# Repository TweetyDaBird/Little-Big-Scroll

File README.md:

# Little Big Scroll

## A family of low-cost and easy to build macro pads. 
Usable for Media control, macro buttons, or just about anything else you can imagine and code in QMK.

### The 'family' includes:
- **Little Big Scroll 4** - 2 or 4 Cherry MX compatible keys, one Ø40 mm encoder with button, optional OLED. (Complete)
- **Little Big Scroll 6** - 6 Cherry MX compatible keys, one Ø40 mm encoder with button. (Complete)
- **Little Big Scroll 8** - 8 Cherry MX compatible keys, one Ø40 mm encoder with button, optional OLED. (Prototype)
- **Little Big Scroll** - A single Ø40 mm encoder wheel with button. (Prototype completed, pending redesign)

### Common specifications
- Use a Promicro or equivalent controller
- Programmable with QMK and VIAL
- Cherry MX style keyswitches
- Kaihl hot swap sockets
- Clickable Rotary encoder with up to 40mm wheel
- Designed with a complete sandwich case for an easy build (If purchased, comes as a complete kit)
- Optional Per Key RGB / Encoder Underglow
- (LBS 4/8) Optional 0.91" 128x32 OLED screen

## Buildguide

### Step-by-step
- Solder hotswap sockets in markings
- Solder capacitors C1, C2 in markings
- **LSB 4 only** - If you are mounting the OLED, solder Resistors R1, R2 & OLED Screen in place
- Solder Encoder
- Solder controller, face up, flush with underside of PCB (*)
- Assemble plate/spacers around the PCB (**)
- Insert switches/caps (remember to support the sockets!) and add encoder wheel
- Program
- Enjoy!

(*) The controller can be socketed, but that adds height, and you need longer spacers than the ones included if purchasing a kit.

(**) For LSB 4, the unused plate forms the bottom, unless a solid backplate is added as an optional extra. Breakaway tabs need to be removed and filed before use.

## Buy a kit!
I sell complete kits, making it easy to build your keyboard, and it also supports prototypes for new wacky ones. 

## Discord for build help and discussions!

## License

[![CC BY-SA 4.0][cc-by-sa-shield]][cc-by-sa] - This work is licensed under a
[Creative Commons Attribution-ShareAlike 4.0 International License][cc-by-sa].

[cc-by-sa]: http://creativecommons.org/licenses/by-sa/4.0/
[cc-by-sa-shield]: https://img.shields.io/badge/License-CC%20BY--SA%204.0-lightgrey.svg

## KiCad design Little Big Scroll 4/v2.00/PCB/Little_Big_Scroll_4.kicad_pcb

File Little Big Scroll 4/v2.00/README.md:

# Little Big Scroll 4 v2

A low-cost and easy to build macro pad intended for among other things media controls. 

- Uses an RP2040 Zero or equivalent controller
- Programmable with QMK and VIAL
- Cherry MX style keyswitches
- Kaihl hot swap sockets
- Clickable Rotary encoder with up to 40mm wheel
- Optional Per Key RGB
- Designed with a complete sandwich case for an easy build

## BOM
| Name of part | Qty. | Remarks | Aliexpress |
| ------------ | ---- | ------- | --------------- |
| PCB          | 1 | 1,6 mm thick | X |
| Plate Front  | 1 |1,6 mm thick| X |
| Plate Rear   | 1 | 1,6 mm thick| X |
| Kailh hotswap socket | 4 | Qty. depends on layout. | [link](https://www.aliexpress.com/item/-/4001051840976.html?spm=a2g0s.8937460.0.0.6f132e0eKYB5RQ&_ga=2.174414626.1036705865.1612730332-979734211.1611132916&_gac=1.119713146.1611132916.CjwKCAiAxp-ABhALEiwAXm6IyZF-HtTdP3MQioG5GOxLvsaJfBbhqTGIQbmV0LXKDx2MZSDJJJTbaBoCPkoQAvD_BwE) |
| Capacitors 100 nF | 2 | Needed for Rotary Encoder. | [link](https://www.aliexpress.com/item/-/32971478818.html?spm=a2g0s.8937460.0.0.6f132e0eKYB5RQ&_ga=2.149198518.1036705865.1612730332-979734211.1611132916&_gac=1.48473428.1611132916.CjwKCAiAxp-ABhALEiwAXm6IyZF-HtTdP3MQioG5GOxLvsaJfBbhqTGIQbmV0LXKDx2MZSDJJJTbaBoCPkoQAvD_BwE) |
| M2 * 7/8 mm standoff | 4 | Round, max 3.7 mm in diameter | [link](https://www.aliexpress.com/item/-/32863484622.html?spm=a2g0s.8937460.0.0.c1b82e0edjrOT3&_ga=2.215809815.1036705865.1612730332-979734211.1611132916&_gac=1.26395343.1611132916.CjwKCAiAxp-ABhALEiwAXm6IyZF-HtTdP3MQioG5GOxLvsaJfBbhqTGIQbmV0LXKDx2MZSDJJJTbaBoCPkoQAvD_BwE) |
| M2 * 4 mm screw | 8 | 4-8 mm length fits, low profile hex head recommended | [link](https://www.aliexpress.com/item/-/32966917947.html?spm=a2g0s.8937460.0.0.c1b82e0edjrOT3&_ga=2.246923140.1036705865.1612730332-979734211.1611132916&_gac=1.263439230.1611132916.CjwKCAiAxp-ABhALEiwAXm6IyZF-HtTdP3MQioG5GOxLvsaJfBbhqTGIQbmV0LXKDx2MZSDJJJTbaBoCPkoQAvD_BwE) |
| Silicon pads | 4 |  | [link](https://www.aliexpress.com/item/-/32912066603.html?spm=a2g0s.8937460.0.0.6f132e0eKYB5RQ&_ga=2.145547188.1036705865.1612730332-979734211.1611132916&_gac=1.57255896.1611132916.CjwKCAiAxp-ABhALEiwAXm6IyZF-HtTdP3MQioG5GOxLvsaJfBbhqTGIQbmV0LXKDx2MZSDJJJTbaBoCPkoQAvD_BwE) |
| RP2040 Zero | 1 | | [link](https://www.aliexpress.com/item/1005003504006451.html) |
| Rotary Encoder | 1 || [link](https://www.aliexpress.com/item/10000056483250.html?spm=a2g0o.productlist.0.0.64951c5fKcPiug&algo_pvid=b530d9b1-fbd2-4598-bf53-bece1343826f&algo_expid=b530d9b1-fbd2-4598-bf53-bece1343826f-2&btsid=2100bdd016135510210168102eefcc&ws_ab_test=searchweb0_0,searchweb201602_,searchweb201603_) |
| Rotary Encoder Knob | 1 | Clearance for max 40 mm diameter, pick halfshaft or spline according to encoder choice.  | [link](https://www.aliexpress.com/item/10000056483250.html?spm=a2g0o.productlist.0.0.64951c5fKcPiug&algo_pvid=b530d9b1-fbd2-4598-bf53-bece1343826f&algo_expid=b530d9b1-fbd2-4598-bf53-bece1343826f-2&btsid=2100bdd016135510210168102eefcc&ws_ab_test=searchweb0_0,searchweb201602_,searchweb201603_) |
| RGB LED's | 6 | **- Optional -** SK6812 mini-E   | [link](https://www.aliexpress.com/item/4000475685852.html) |

## Buildguide

### Step-by-step
- Solder hotswap sockets in markings on rear of PCB
- Solder capacitors C1, C2 in markings on rear of PCB
- Solder Encoder (Place from front, solder on the back)
- Solder controller (**Place behind the PCB**, buttons facing up).
- Assemble plate & spacers.
- Insert switches and add encoder wheel
- Program
- Enjoy!

## License
[![CC BY-SA 4.0][cc-by-sa-shield]][cc-by-sa]  -  This work is licensed under a
[Creative Commons Attribution-ShareAlike 4.0 International License][cc-by-sa].

[cc-by-sa]: http://creativecommons.org/licenses/by-sa/4.0/
[cc-by-sa-image]: https://licensebuttons.net/l/by-sa/4.0/88x31.png
[cc-by-sa-shield]: https://img.shields.io/badge/License-CC%20BY--SA%204.0-lightgrey.svg

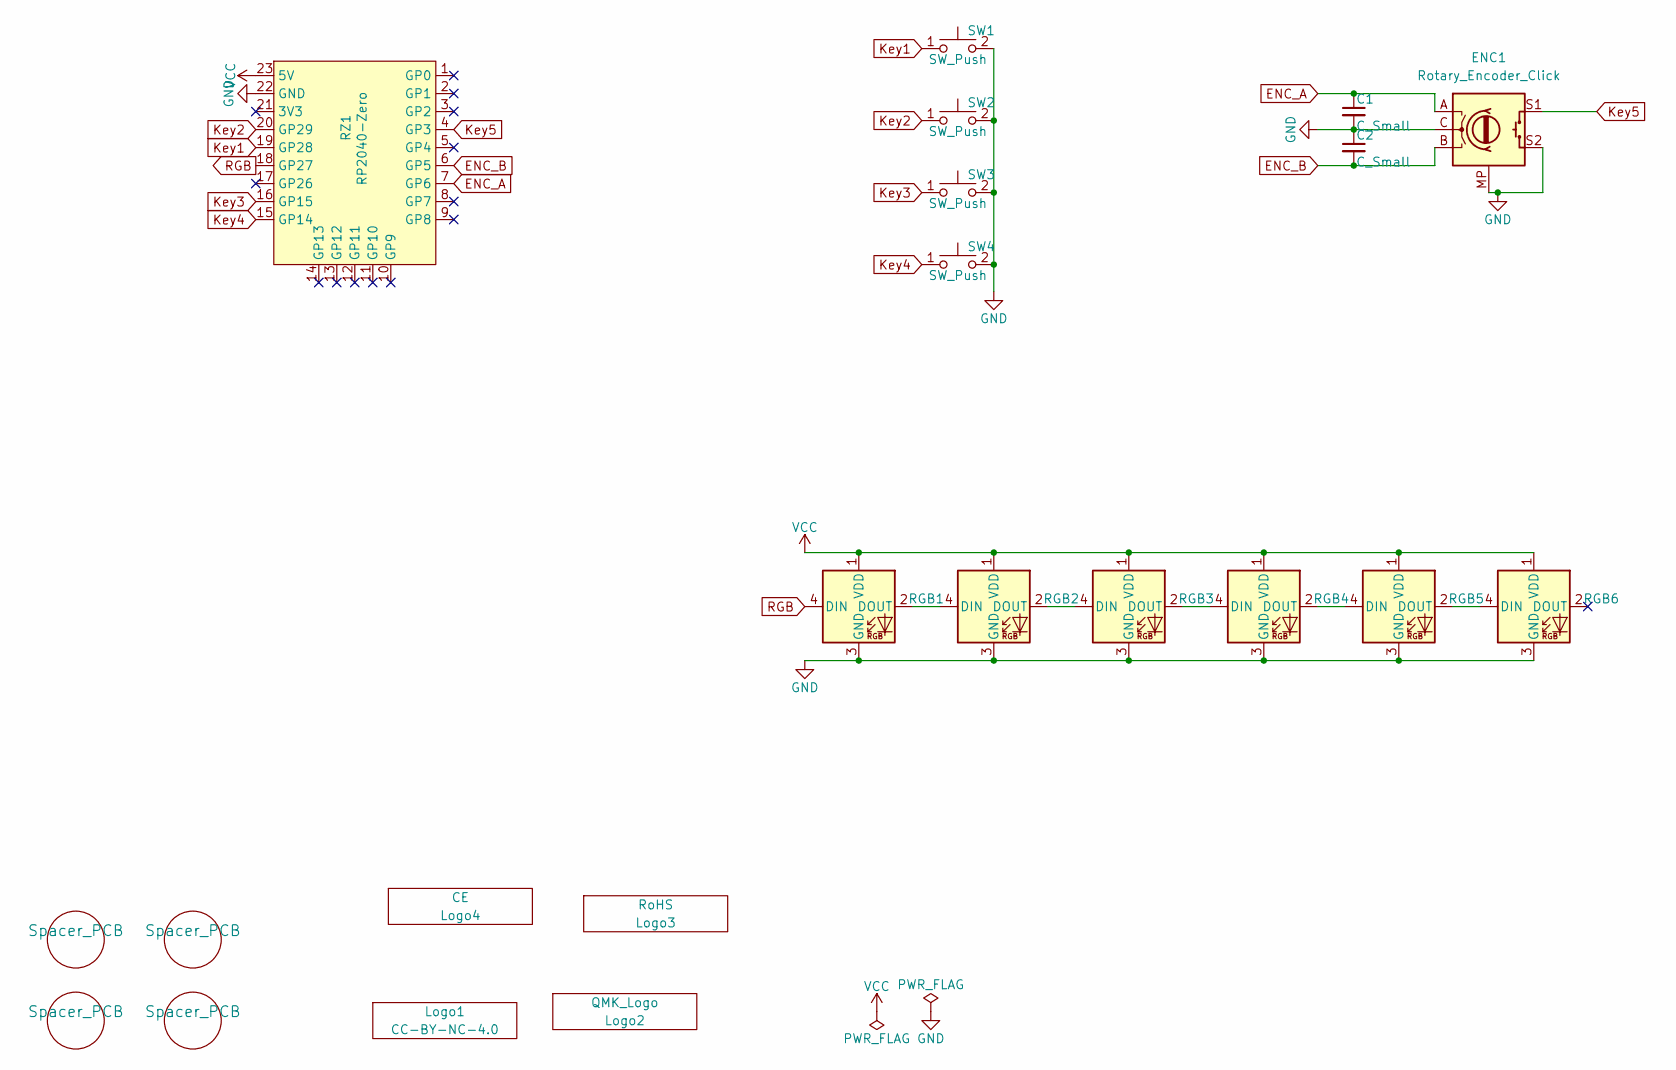
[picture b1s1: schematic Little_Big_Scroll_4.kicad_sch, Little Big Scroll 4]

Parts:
C1, C2: C_Small
ENC1: Rotary_Encoder_Click; Encoder_Alps_EC11E_Small
H1, H2, H3, H4: Spacer_PCB; Spacer PCB hole
Logo1: CC-BY-NC-4.0; CC_BY_SA_40_line
Logo2: QMK_Logo; Powered_by_QMK
Logo3: RoHS; RoHs
Logo4: CE
RGB1, RGB2, RGB3, RGB4, RGB5, RGB6: SK6812MINI-E; RGB_SK6812MINI-E
RZ1: RP2040-Zero
SW1, SW2, SW3, SW4: SW_Push; SW_MX_HotSwap

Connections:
ENC_A: C1.1, ENC1.A, RZ1.7 (GP6)
ENC_B: C2.2, ENC1.B, RZ1.6 (GP5)
GND: C1.2, C2.1, ENC1.C, ENC1.MP (GND), ENC1.S2, RGB1.3 (GND), RGB2.3 (GND), RGB3.3 (GND), RGB4.3 (GND), RGB5.3 (GND), RGB6.3 (GND), RZ1.22 (GND), SW1.2, SW2.2, SW3.2, SW4.2
Key1: RZ1.19 (GP28), SW1.1
Key2: RZ1.20 (GP29), SW2.1
Key3: RZ1.16 (GP15), SW3.1
Key4: RZ1.15 (GP14), SW4.1
Key5: ENC1.S1, RZ1.4 (GP3)
unnamed: RGB1.2 (DOUT), RGB2.4 (DIN)
unnamed: RGB2.2 (DOUT), RGB3.4 (DIN)
unnamed: RGB3.2 (DOUT), RGB4.4 (DIN)
unnamed: RGB4.2 (DOUT), RGB5.4 (DIN)
unnamed: RGB5.2 (DOUT), RGB6.4 (DIN)
RGB: RGB1.4 (DIN), RZ1.18 (GP27)
VCC: RGB1.1 (VDD), RGB2.1 (VDD), RGB3.1 (VDD), RGB4.1 (VDD), RGB5.1 (VDD), RGB6.1 (VDD), RZ1.23 (5V)

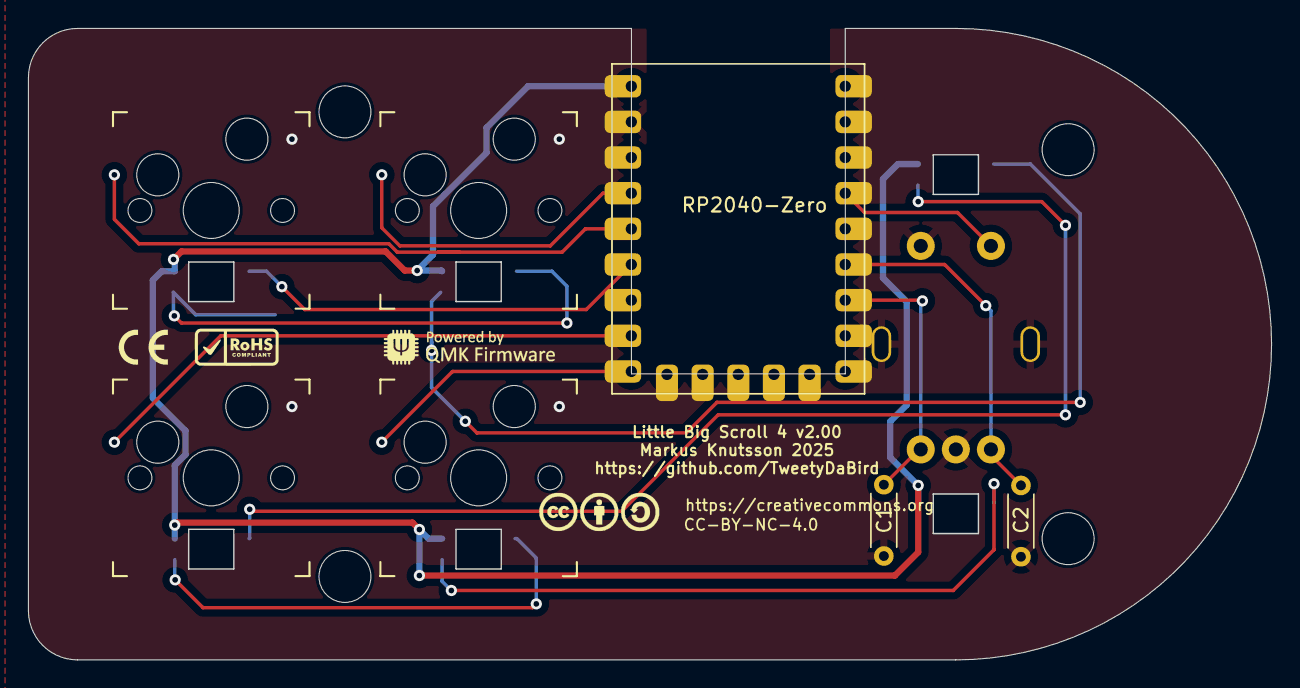
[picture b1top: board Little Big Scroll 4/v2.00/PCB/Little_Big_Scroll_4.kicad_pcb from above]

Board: 2 copper layers, 88.5 x 44.9 mm, 22 parts (0 on the bottom side), 15 nets.

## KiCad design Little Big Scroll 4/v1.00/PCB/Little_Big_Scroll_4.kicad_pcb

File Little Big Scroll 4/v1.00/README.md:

# Little Big Scroll 4

A low-cost and easy to build macro pad intended for among other things media controls. 

- Uses a Promicro/Elite C or equivalent controller
- Programmable with QMK and VIAL
- Cherry MX style keyswitches
- Kaihl hot swap sockets
- Clickable Rotary encoder with up to 40mm wheel
- Optional 0.91" 128x32 OLED screen
- Optional Per Key RGB
- Designed with a complete sandwich case for an easy build

## BOM
| Name of part | Qty. | Remarks | Aliexpress |
| ------------ | ---- | ------- | --------------- |
| PCB          | 1 | 1,6 mm thick | X |
| Plate 4-Key  | 1 |1,6 mm thick| X |
| Plate OLED   | 1 | 1,6 mm thick| X |
| Kailh hotswap socket | 4 | Qty. depends on layout. | [link](https://www.aliexpress.com/item/-/4001051840976.html?spm=a2g0s.8937460.0.0.6f132e0eKYB5RQ&_ga=2.174414626.1036705865.1612730332-979734211.1611132916&_gac=1.119713146.1611132916.CjwKCAiAxp-ABhALEiwAXm6IyZF-HtTdP3MQioG5GOxLvsaJfBbhqTGIQbmV0LXKDx2MZSDJJJTbaBoCPkoQAvD_BwE) |
| Capacitors 100 nF | 2 | Needed for Rotary Encoder. | [link](https://www.aliexpress.com/item/-/32971478818.html?spm=a2g0s.8937460.0.0.6f132e0eKYB5RQ&_ga=2.149198518.1036705865.1612730332-979734211.1611132916&_gac=1.48473428.1611132916.CjwKCAiAxp-ABhALEiwAXm6IyZF-HtTdP3MQioG5GOxLvsaJfBbhqTGIQbmV0LXKDx2MZSDJJJTbaBoCPkoQAvD_BwE) |
| Resistor 4.7 kOhm | 2 | **- Optional -** Needed for OLED screen. | [link](https://www.aliexpress.com/item/-/32847047012.html?spm=a2g0s.8937460.0.0.c1b82e0edjrOT3&_ga=2.241041155.1036705865.1612730332-979734211.1611132916&_gac=1.219449963.1611132916.CjwKCAiAxp-ABhALEiwAXm6IyZF-HtTdP3MQioG5GOxLvsaJfBbhqTGIQbmV0LXKDx2MZSDJJJTbaBoCPkoQAvD_BwE) |
| 0.91" OLED Display | 1 | **- Optional -** Qty. depends on layout. | [link](https://www.aliexpress.com/item/-/4001028384269.html?spm=a2g0s.8937460.0.0.c1b82e0edjrOT3&_ga=2.241041155.1036705865.1612730332-979734211.1611132916&_gac=1.219449963.1611132916.CjwKCAiAxp-ABhALEiwAXm6IyZF-HtTdP3MQioG5GOxLvsaJfBbhqTGIQbmV0LXKDx2MZSDJJJTbaBoCPkoQAvD_BwE) |
| M2 * 7/8 mm standoff | 4 | Round, max 3.7 mm in diameter | [link](https://www.aliexpress.com/item/-/32863484622.html?spm=a2g0s.8937460.0.0.c1b82e0edjrOT3&_ga=2.215809815.1036705865.1612730332-979734211.1611132916&_gac=1.26395343.1611132916.CjwKCAiAxp-ABhALEiwAXm6IyZF-HtTdP3MQioG5GOxLvsaJfBbhqTGIQbmV0LXKDx2MZSDJJJTbaBoCPkoQAvD_BwE) |
| M2 * 4 mm screw | 8 | 4-8 mm length fits, low profile hex head recommended | [link](https://www.aliexpress.com/item/-/32966917947.html?spm=a2g0s.8937460.0.0.c1b82e0edjrOT3&_ga=2.246923140.1036705865.1612730332-979734211.1611132916&_gac=1.263439230.1611132916.CjwKCAiAxp-ABhALEiwAXm6IyZF-HtTdP3MQioG5GOxLvsaJfBbhqTGIQbmV0LXKDx2MZSDJJJTbaBoCPkoQAvD_BwE) |
| Silicon pads | 4 |  | [link](https://www.aliexpress.com/item/-/32912066603.html?spm=a2g0s.8937460.0.0.6f132e0eKYB5RQ&_ga=2.145547188.1036705865.1612730332-979734211.1611132916&_gac=1.57255896.1611132916.CjwKCAiAxp-ABhALEiwAXm6IyZF-HtTdP3MQioG5GOxLvsaJfBbhqTGIQbmV0LXKDx2MZSDJJJTbaBoCPkoQAvD_BwE) |
| Pro Micro | 1 | Can be built with various ProMicro clones as well as Elite C | [link](https://www.aliexpress.com/item/-/32849563958.html?spm=a2g0s.8937460.0.0.c1b82e0edjrOT3&_ga=2.175422242.1036705865.1612730332-979734211.1611132916&_gac=1.225165928.1611132916.CjwKCAiAxp-ABhALEiwAXm6IyZF-HtTdP3MQioG5GOxLvsaJfBbhqTGIQbmV0LXKDx2MZSDJJJTbaBoCPkoQAvD_BwE) |
| Rotary Encoder | 1 || [link](https://www.aliexpress.com/item/10000056483250.html?spm=a2g0o.productlist.0.0.64951c5fKcPiug&algo_pvid=b530d9b1-fbd2-4598-bf53-bece1343826f&algo_expid=b530d9b1-fbd2-4598-bf53-bece1343826f-2&btsid=2100bdd016135510210168102eefcc&ws_ab_test=searchweb0_0,searchweb201602_,searchweb201603_) |
| Rotary Encoder Knob | 1 | Clearance for max 40 mm diameter, pick halfshaft or spline according to encoder choice.  | [link](https://www.aliexpress.com/item/10000056483250.html?spm=a2g0o.productlist.0.0.64951c5fKcPiug&algo_pvid=b530d9b1-fbd2-4598-bf53-bece1343826f&algo_expid=b530d9b1-fbd2-4598-bf53-bece1343826f-2&btsid=2100bdd016135510210168102eefcc&ws_ab_test=searchweb0_0,searchweb201602_,searchweb201603_) |
| RGB LED's | 6 | **- Optional -** SK6812 mini-E   | [link](https://www.aliexpress.com/item/4000475685852.html) |

## Buildguide

### Step-by-step
- Solder hotswap sockets in markings
- Solder capacitors C1, C2 in markings
- **Optional:** Solder Resistors R1, R2 & OLED Screen
- Solder Encoder
- Solder controller, face up, flush with underside of PCB.
- Prepare the front plate you're using by removing tabs and filing.
- Assemble plate/spacers, unused plate forms the bottom.
- Insert switches and add encoder wheel
- Program
- Enjoy!

## License
[![CC BY-SA 4.0][cc-by-sa-shield]][cc-by-sa]  -  This work is licensed under a
[Creative Commons Attribution-ShareAlike 4.0 International License][cc-by-sa].

[cc-by-sa]: http://creativecommons.org/licenses/by-sa/4.0/
[cc-by-sa-image]: https://licensebuttons.net/l/by-sa/4.0/88x31.png
[cc-by-sa-shield]: https://img.shields.io/badge/License-CC%20BY--SA%204.0-lightgrey.svg

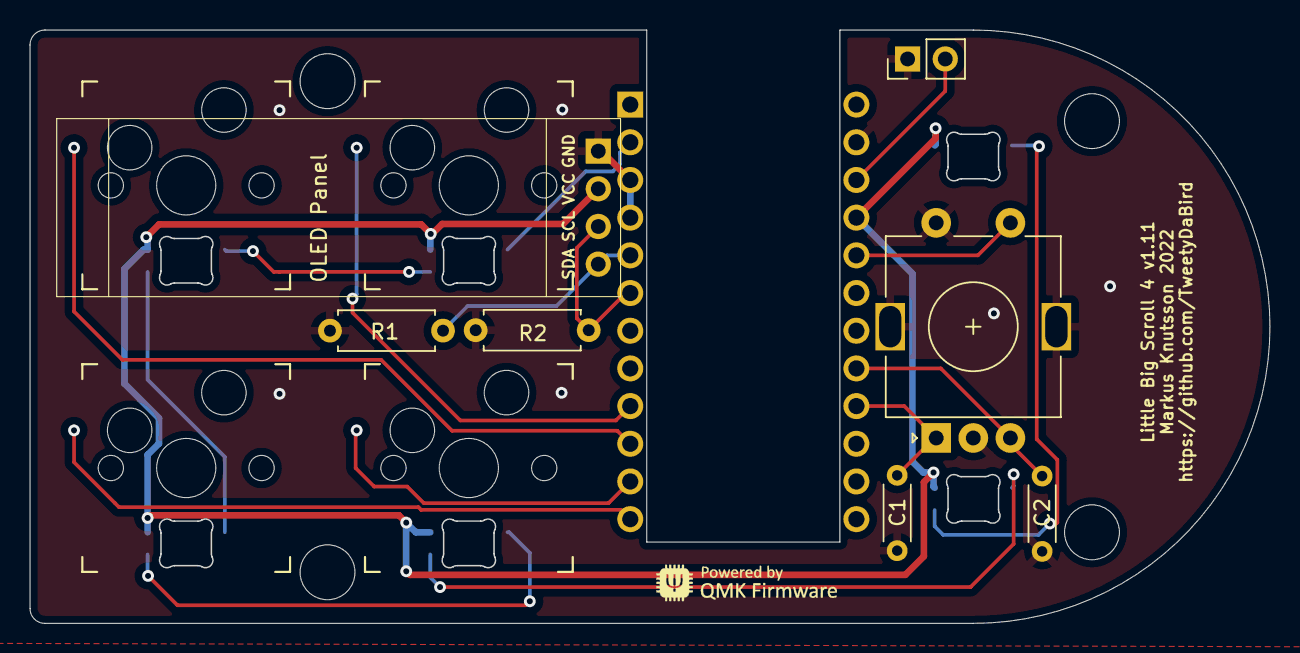
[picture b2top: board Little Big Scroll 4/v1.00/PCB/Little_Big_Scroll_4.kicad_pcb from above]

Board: 2 copper layers, 83.5 x 39.9 mm, 24 parts (1 on the bottom side), 18 nets.

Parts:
C1, C2: 100nF; R_Axial_DIN0204_L3.6mm_D1.6mm_P5.08mm_Horizontal
H1, H2, H3, H4: Hole; MountingHole_3.7mm
J1: Conn_01x02; PinHeader_1x02_P2.54mm_Vertical
LED1, LED2, LED3, LED4, LED5, LED6: SK6812MINI-E; MX_SK6812MINI-E
Lic1: CC-BY-SA_4.0; CC_BY_SA_40
Logo1: QMK_Logo; Powered_by_QMK
OLED1: OLED_4pin; SSD1306-0.91-OLED-4pin-128x32
R1, R2: 4K7; R_Axial_DIN0207_L6.3mm_D2.5mm_P7.62mm_Horizontal
SW1, SW2, SW3, SW4: SW_Push; Kailh_socket_MX_RGB
SW5: Rotary_Encoder_Switch; RotaryEncoder_Alps_EC11E-Switch_Vertical_H20mm
U1: ProMicro; ArduinoProMicro-BackSide

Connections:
ENC_A: C1.1, SW5.A, U1.16 (15/PB1)
ENC_B: C2.2, SW5.B, U1.17 (A0/PF7)
GND: C1.2, C2.1, J1.1, LED1.3 (GND), LED2.3 (GND), LED3.3 (GND), LED4.3 (GND), LED5.3 (GND), LED6.3 (GND), OLED1.1 (GND), R1.2, R2.2, SW1.1, SW2.1, SW3.1, SW4.1, SW5.C, SW5.MP1 (GND), SW5.MP2 (GND), SW5.S2, U1.3 (GND), U1.4 (GND), U1.23 (GND)
Key1: SW1.2, U1.10 (7/PE6)
Key2: SW2.2, U1.9 (6/PD7)
Key3: SW3.2, U1.12 (9/PB5)
Key4: SW4.2, U1.11 (8/PB4)
Key5: SW5.S1, U1.20 (A3/PF4)
unnamed: J1.2, U1.22 (RST)
unnamed: LED1.2 (DOUT), LED2.4 (DIN)
unnamed: LED2.2 (DOUT), LED3.4 (DIN)
unnamed: LED3.2 (DOUT), LED4.4 (DIN)
unnamed: LED4.2 (DOUT), LED5.4 (DIN)
unnamed: LED5.2 (DOUT), LED6.4 (DIN)
RGB: LED1.4 (DIN), U1.2 (RX1/PD2)
SCL: OLED1.3 (SCL), R2.1, U1.6 (3/PD0)
SDA: OLED1.4 (SDA), R1.1, U1.5 (2/PD1)
VCC: LED1.1 (VCC), LED2.1 (VCC), LED3.1 (VCC), LED4.1 (VCC), LED5.1 (VCC), LED6.1 (VCC), OLED1.2 (VCC), U1.21 (VCC)

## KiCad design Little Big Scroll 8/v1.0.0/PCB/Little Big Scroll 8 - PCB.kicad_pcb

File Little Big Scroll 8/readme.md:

# Little Big Scroll 8

A low-cost and easy to build macro pad intended for amongst other things media controls. 

- Uses a Promicro or equivalent controller
- Programmable with QMK and VIAL
- Cherry MX style keyswitches
- Kaihl hot swap sockets
- Clickable Rotary encoder with up to 40mm wheel
- Optional Per Key RGB
- Designed with a complete sandwich case for an easy build

## BOM
| Name of part | Qty. | Remarks | Aliexpress |
| ------------ | ---- | ------- | --------------- |
| PCB          | 1 | 1,6 mm thick | X |
| Front Plate  | 1 |1,6 mm thick| X |
| Rear Plate   | 1 | 1,6 mm thick| X |
| Kailh hotswap socket | 8 | | [link](https://www.aliexpress.com/item/-/4001051840976.html?spm=a2g0s.8937460.0.0.6f132e0eKYB5RQ&_ga=2.174414626.1036705865.1612730332-979734211.1611132916&_gac=1.119713146.1611132916.CjwKCAiAxp-ABhALEiwAXm6IyZF-HtTdP3MQioG5GOxLvsaJfBbhqTGIQbmV0LXKDx2MZSDJJJTbaBoCPkoQAvD_BwE) |
| Capacitors 100 nF | 2 | Needed for Rotary Encoder. | [link](https://www.aliexpress.com/item/-/32971478818.html?spm=a2g0s.8937460.0.0.6f132e0eKYB5RQ&_ga=2.149198518.1036705865.1612730332-979734211.1611132916&_gac=1.48473428.1611132916.CjwKCAiAxp-ABhALEiwAXm6IyZF-HtTdP3MQioG5GOxLvsaJfBbhqTGIQbmV0LXKDx2MZSDJJJTbaBoCPkoQAvD_BwE) |
| M2 * 7/8 mm standoff | 4 | Round, max 3.7 mm in diameter | [link](https://www.aliexpress.com/item/-/32863484622.html?spm=a2g0s.8937460.0.0.c1b82e0edjrOT3&_ga=2.215809815.1036705865.1612730332-979734211.1611132916&_gac=1.26395343.1611132916.CjwKCAiAxp-ABhALEiwAXm6IyZF-HtTdP3MQioG5GOxLvsaJfBbhqTGIQbmV0LXKDx2MZSDJJJTbaBoCPkoQAvD_BwE) |
| M2 * 4 mm screw | 8 | 4-8 mm length fits, low profile hex head recommended | [link](https://www.aliexpress.com/item/-/32966917947.html?spm=a2g0s.8937460.0.0.c1b82e0edjrOT3&_ga=2.246923140.1036705865.1612730332-979734211.1611132916&_gac=1.263439230.1611132916.CjwKCAiAxp-ABhALEiwAXm6IyZF-HtTdP3MQioG5GOxLvsaJfBbhqTGIQbmV0LXKDx2MZSDJJJTbaBoCPkoQAvD_BwE) |
| Silicon pads | 4 |  | [link](https://www.aliexpress.com/item/-/32912066603.html?spm=a2g0s.8937460.0.0.6f132e0eKYB5RQ&_ga=2.145547188.1036705865.1612730332-979734211.1611132916&_gac=1.57255896.1611132916.CjwKCAiAxp-ABhALEiwAXm6IyZF-HtTdP3MQioG5GOxLvsaJfBbhqTGIQbmV0LXKDx2MZSDJJJTbaBoCPkoQAvD_BwE) |
| Pro Micro | 1 | Can be built with various ProMicro clones as well as Elite C | [link](https://www.aliexpress.com/item/-/32849563958.html?spm=a2g0s.8937460.0.0.c1b82e0edjrOT3&_ga=2.175422242.1036705865.1612730332-979734211.1611132916&_gac=1.225165928.1611132916.CjwKCAiAxp-ABhALEiwAXm6IyZF-HtTdP3MQioG5GOxLvsaJfBbhqTGIQbmV0LXKDx2MZSDJJJTbaBoCPkoQAvD_BwE) |
| Rotary Encoder | 1 || [link](https://www.aliexpress.com/item/10000056483250.html?spm=a2g0o.productlist.0.0.64951c5fKcPiug&algo_pvid=b530d9b1-fbd2-4598-bf53-bece1343826f&algo_expid=b530d9b1-fbd2-4598-bf53-bece1343826f-2&btsid=2100bdd016135510210168102eefcc&ws_ab_test=searchweb0_0,searchweb201602_,searchweb201603_) |
| Rotary Encoder Knob | 1 | Clearance for max 40 mm diameter, pick halfshaft or spline according to encoder choice.  | [link](https://www.aliexpress.com/item/10000056483250.html?spm=a2g0o.productlist.0.0.64951c5fKcPiug&algo_pvid=b530d9b1-fbd2-4598-bf53-bece1343826f&algo_expid=b530d9b1-fbd2-4598-bf53-bece1343826f-2&btsid=2100bdd016135510210168102eefcc&ws_ab_test=searchweb0_0,searchweb201602_,searchweb201603_) |
| RGB LED's | 8 | **- Optional -** SK6812 mini-E   | [link](https://www.aliexpress.com/item/4000475685852.html) |
| 0.91" OLED Display | 1 | **- Optional -** Qty. depends on layout. | [link](https://www.aliexpress.com/item/-/4001028384269.html?spm=a2g0s.8937460.0.0.c1b82e0edjrOT3&_ga=2.241041155.1036705865.1612730332-979734211.1611132916&_gac=1.219449963.1611132916.CjwKCAiAxp-ABhALEiwAXm6IyZF-HtTdP3MQioG5GOxLvsaJfBbhqTGIQbmV0LXKDx2MZSDJJJTbaBoCPkoQAvD_BwE) |

## Buildguide

### Step-by-step
- Solder hotswap sockets in markings
- Solder capacitors C1, C2 in markings
- Solder Encoder
- Solder controller, face up, flush with underside of PCB
- Assemble plate/spacers
- Insert switches and add encoder wheel
- Program
- Enjoy!

## License
[![CC BY-SA 4.0][cc-by-sa-shield]][cc-by-sa]  -  This work is licensed under a
[Creative Commons Attribution-ShareAlike 4.0 International License][cc-by-sa].

[cc-by-sa]: http://creativecommons.org/licenses/by-sa/4.0/
[cc-by-sa-image]: https://licensebuttons.net/l/by-sa/4.0/88x31.png
[cc-by-sa-shield]: https://img.shields.io/badge/License-CC%20BY--SA%204.0-lightgrey.svg

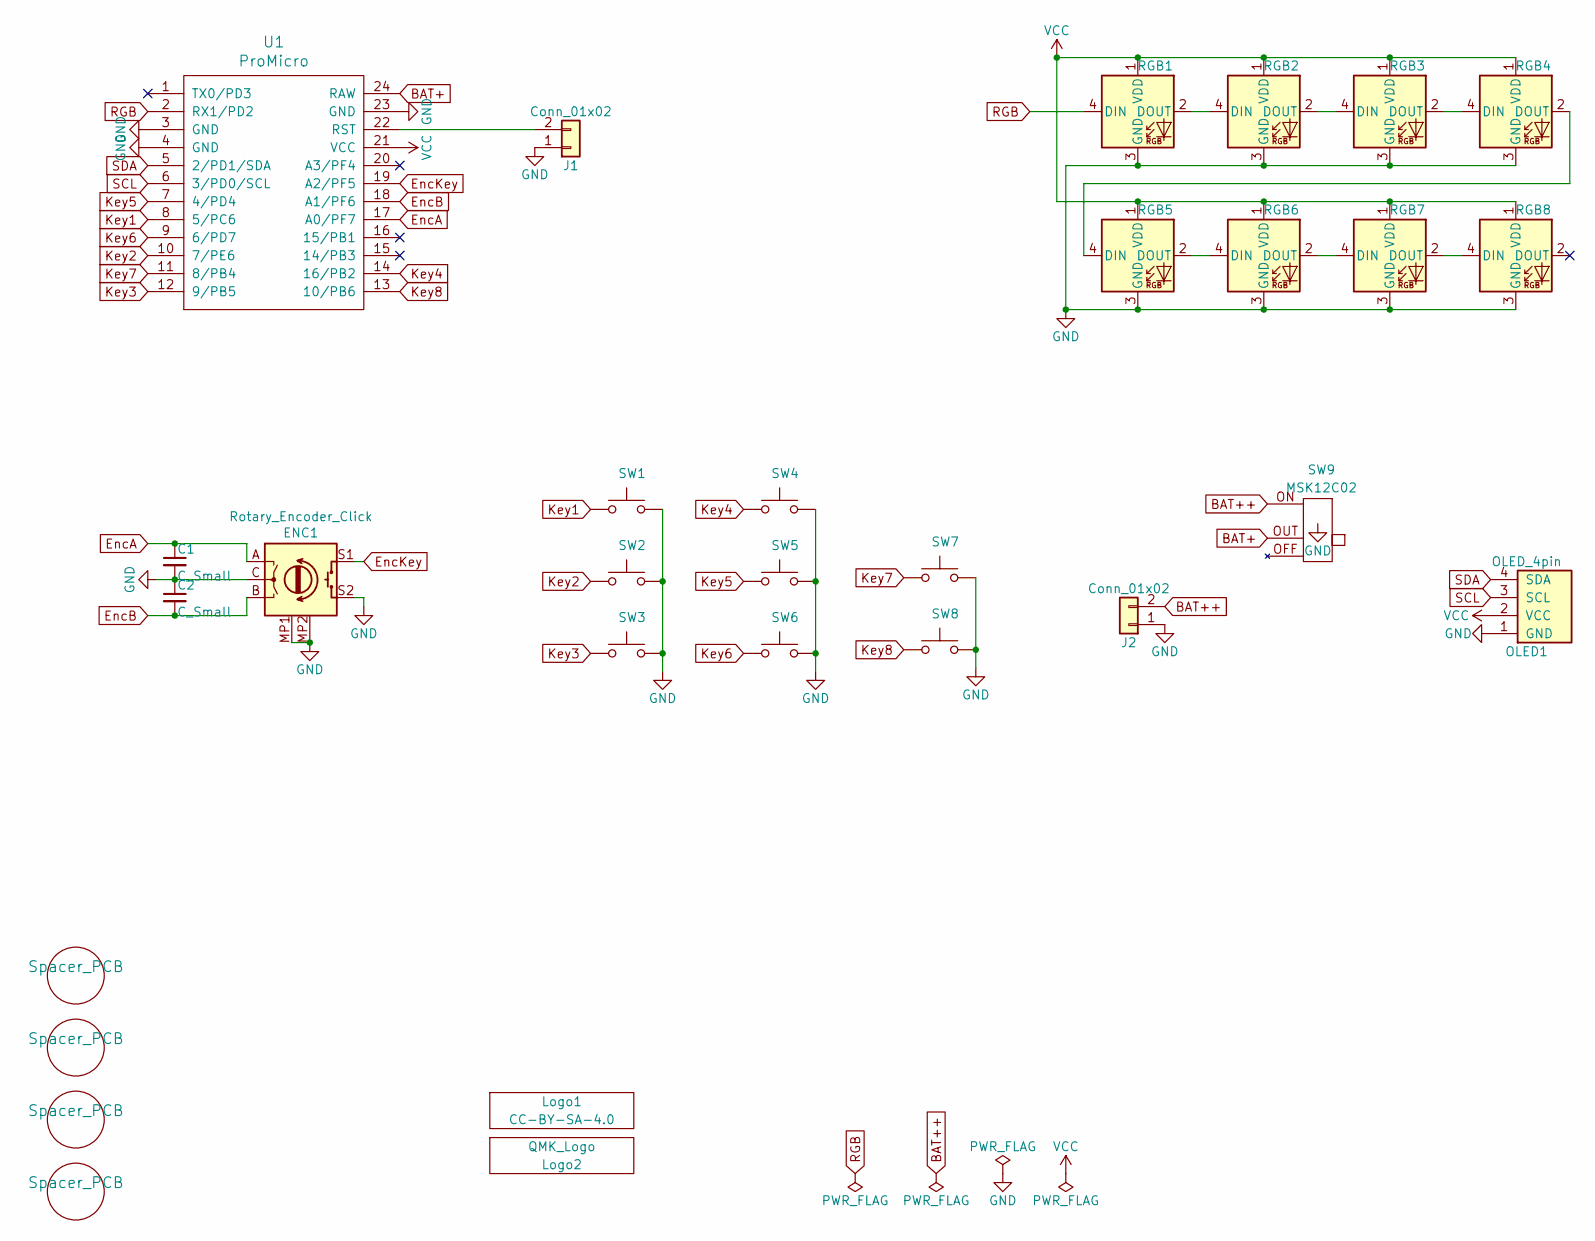
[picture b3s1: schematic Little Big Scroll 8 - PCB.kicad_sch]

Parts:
C1, C2: C_Small; C_Axial_L3.8mm_D2.6mm_P7.50mm_Horizontal
ENC1: Rotary_Encoder_Click; Encoder_Alps_EC11E_Small
H1, H2, H3, H4: Spacer_PCB; Spacer PCB hole
J1: Conn_01x02; PinHeader_1x02_P2.54mm_Vertical
J2: Conn_01x02; JST_PH_S2B-PH-K_1x02_P2.00mm_Horizontal
Logo1: CC-BY-SA-4.0; CC_BY_SA_40
Logo2: QMK_Logo; Powered_by_QMK
OLED1: OLED_4pin; SSD1306-0.91-OLED-4pin-128x32
RGB1, RGB2, RGB3, RGB4, RGB5, RGB6, RGB7, RGB8: SK6812MINI-E; RGB_SK6812MINI-E
SW1, SW2, SW3, SW4, SW5, SW6, SW7, SW8: SW_MX_HotSwap
SW9: MSK12C02
U1: ProMicro; ArduinoProMicro-BackSide

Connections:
BAT+: SW9.OUT, U1.24 (RAW)
BAT++: J2.2, SW9.ON
EncA: C1.1, ENC1.A, U1.17 (A0/PF7)
EncB: C2.2, ENC1.B, U1.18 (A1/PF6)
EncKey: ENC1.S1, U1.19 (A2/PF5)
GND: C1.2, C2.1, ENC1.C, ENC1.MP1 (GND), ENC1.MP2 (GND), ENC1.S2, J1.1, J2.1, OLED1.1 (GND), RGB1.3 (GND), RGB2.3 (GND), RGB3.3 (GND), RGB4.3 (GND), RGB5.3 (GND), RGB6.3 (GND), RGB7.3 (GND), RGB8.3 (GND), SW1.2, SW2.2, SW3.2, SW4.2, SW5.2, SW6.2, SW7.2, SW8.2, SW9.MP (GND), U1.3 (GND), U1.4 (GND), U1.23 (GND)
Key1: SW1.1, U1.8 (5/PC6)
Key2: SW2.1, U1.10 (7/PE6)
Key3: SW3.1, U1.12 (9/PB5)
Key4: SW4.1, U1.14 (16/PB2)
Key5: SW5.1, U1.7 (4/PD4)
Key6: SW6.1, U1.9 (6/PD7)
Key7: SW7.1, U1.11 (8/PB4)
Key8: SW8.1, U1.13 (10/PB6)
unnamed: J1.2, U1.22 (RST)
unnamed: RGB1.2 (DOUT), RGB2.4 (DIN)
unnamed: RGB2.2 (DOUT), RGB3.4 (DIN)
unnamed: RGB3.2 (DOUT), RGB4.4 (DIN)
unnamed: RGB5.2 (DOUT), RGB6.4 (DIN)
unnamed: RGB4.2 (DOUT), RGB5.4 (DIN)
unnamed: RGB6.2 (DOUT), RGB7.4 (DIN)
unnamed: RGB7.2 (DOUT), RGB8.4 (DIN)
RGB: RGB1.4 (DIN), U1.2 (RX1/PD2)
SCL: OLED1.3 (SCL), U1.6 (3/PD0/SCL)
SDA: OLED1.4 (SDA), U1.5 (2/PD1/SDA)
VCC: OLED1.2 (VCC), RGB1.1 (VDD), RGB2.1 (VDD), RGB3.1 (VDD), RGB4.1 (VDD), RGB5.1 (VDD), RGB6.1 (VDD), RGB7.1 (VDD), RGB8.1 (VDD), U1.21 (VCC)

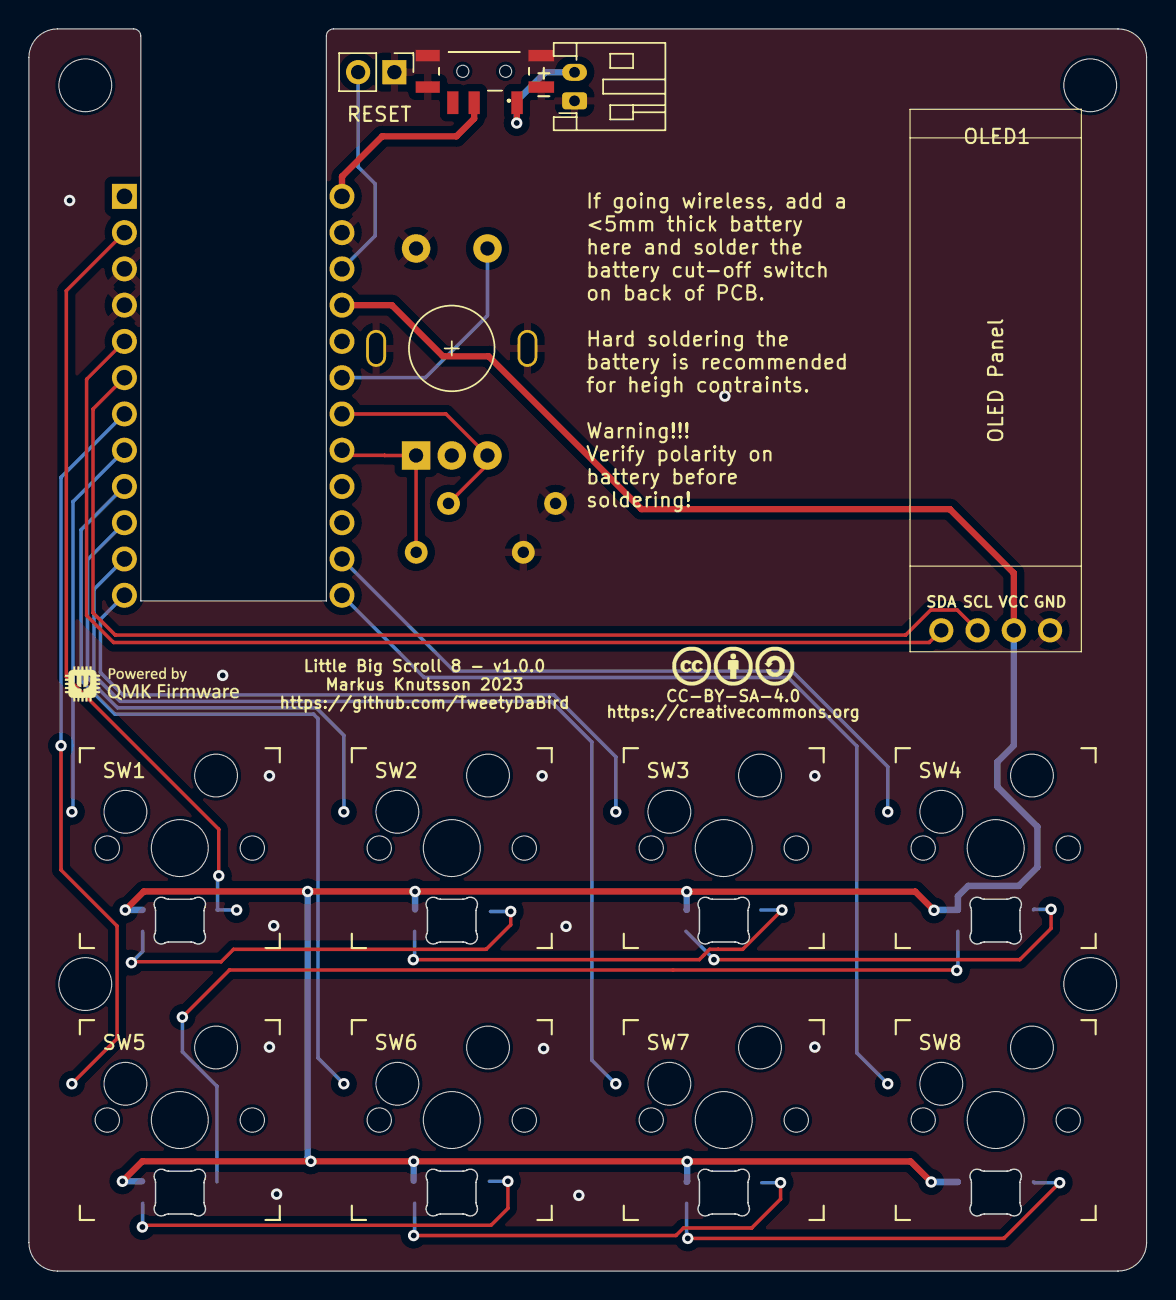
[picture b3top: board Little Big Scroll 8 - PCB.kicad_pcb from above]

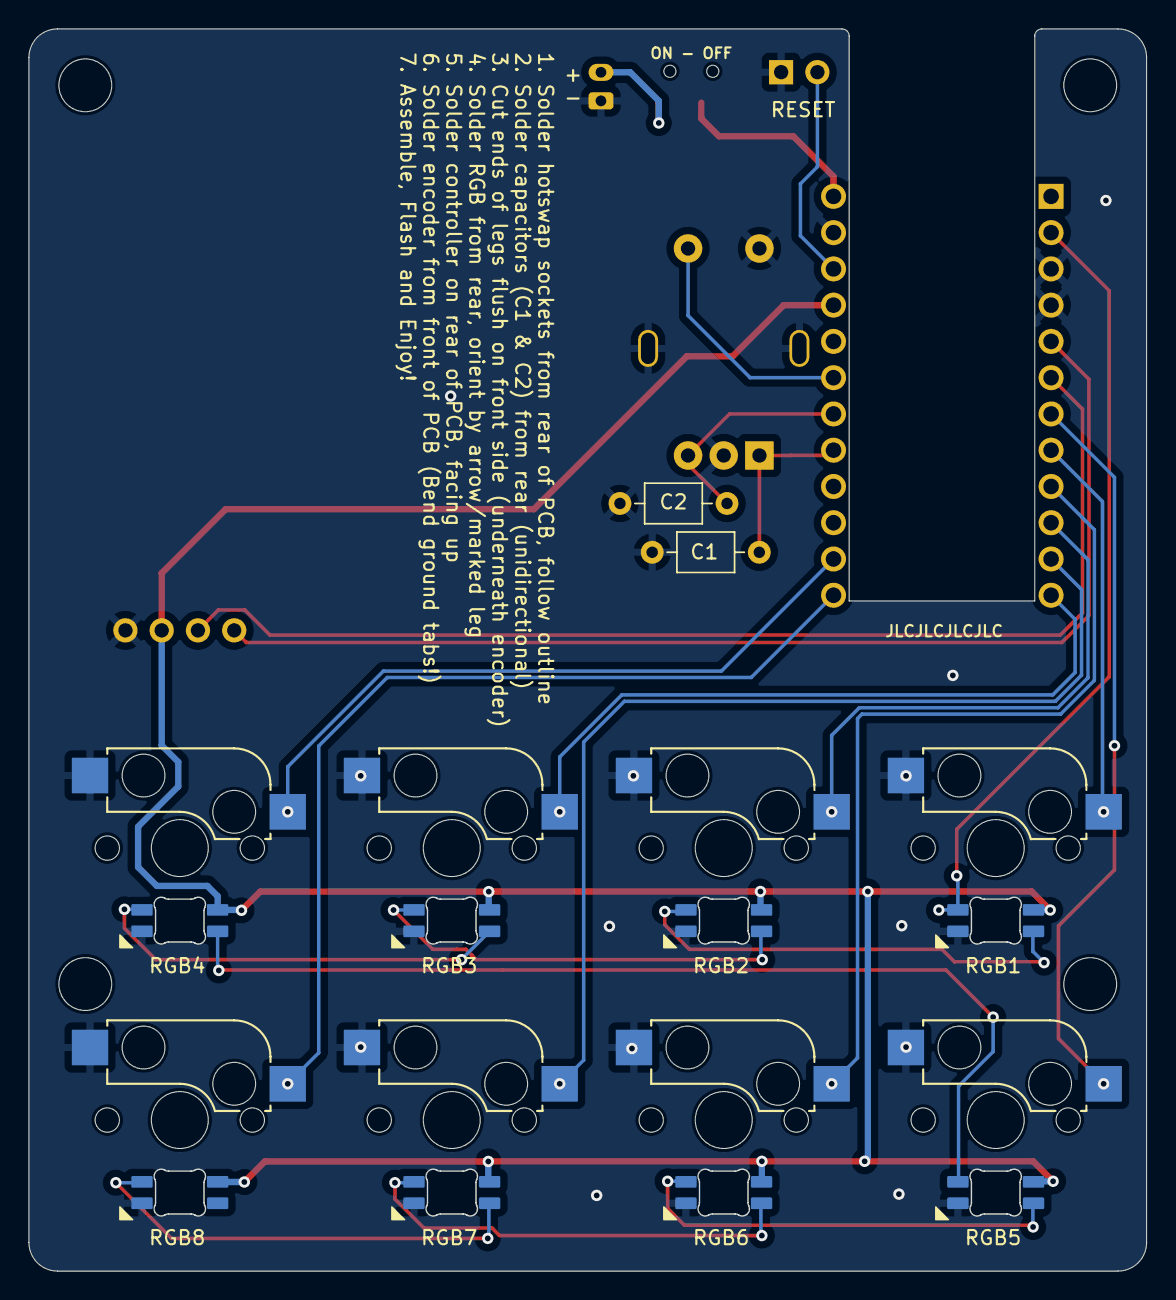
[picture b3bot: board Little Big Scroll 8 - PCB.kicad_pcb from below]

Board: 2 copper layers, 78.2 x 87.0 mm, 30 parts (2 on the bottom side), 26 nets.

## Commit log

2021-12-02 Create LICENSE
2021-12-02 Removed old renders
2021-12-02 Add renders
2021-12-02 Update LICENSE
2021-12-02 folders
2021-12-02 Renamed folders
2021-12-13 Added licensing on PCB
2022-01-10 Tweaked for v1.1
2022-01-10 addedimages
2022-01-10 moved to subfolder
2022-01-10 Added basic VIAL firmware
2022-01-18 Renamed to 'Little Big Scroll 4'
2022-02-02 Added Little Big Scroll 6
2022-03-22 LBS6 v1.01
2022-03-22 cleanup
2022-07-11 LSB6 1.01
2022-09-13 LSB6 Prototype v1.1
2022-09-13 LSB6 v1.1
2022-09-16 LBS6 v1.1.1
    Fixed plate holes
2022-10-18 Updated LBS4 Schematic
2022-10-18 Updated LBS6 Schematic
2022-10-18 Added VIAL firmware files
2023-04-05 Add LBS8
    Initial Commit LBS8
2023-04-05 Revert "Add LBS8"
    This reverts commit 78488f02631a9500abe6f1903c904799e5b784ae.
2023-04-05 Revert "Update README.md"
    This reverts commit b204675a3f5ab89005524fa921e8e21263bfae54.
2023-04-05 Revert "Update README.md"
    This reverts commit c936d279af20137f34751755125480435f59d15c.
2024-05-28 LBS 8
    initial
2025-03-28 LBS 4 v2
2025-06-03 LSB 4 v2
    Initial design
2025-06-03 Removed WIP from main

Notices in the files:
Little Big Scroll 4/v1.00/PCB/Little_Big_Scroll_4.kicad_pcb:
Licensed under Creative Commons Attribution-ShareAlike 4.0 International
Little Big Scroll 8/v1.0.0/PCB/Little Big Scroll 8 - PCB.kicad_pcb:
Licensed under Creative Commons BY-SA 4.0 International
parts and their libraries:
CC-BY-NC-SA-4.0
